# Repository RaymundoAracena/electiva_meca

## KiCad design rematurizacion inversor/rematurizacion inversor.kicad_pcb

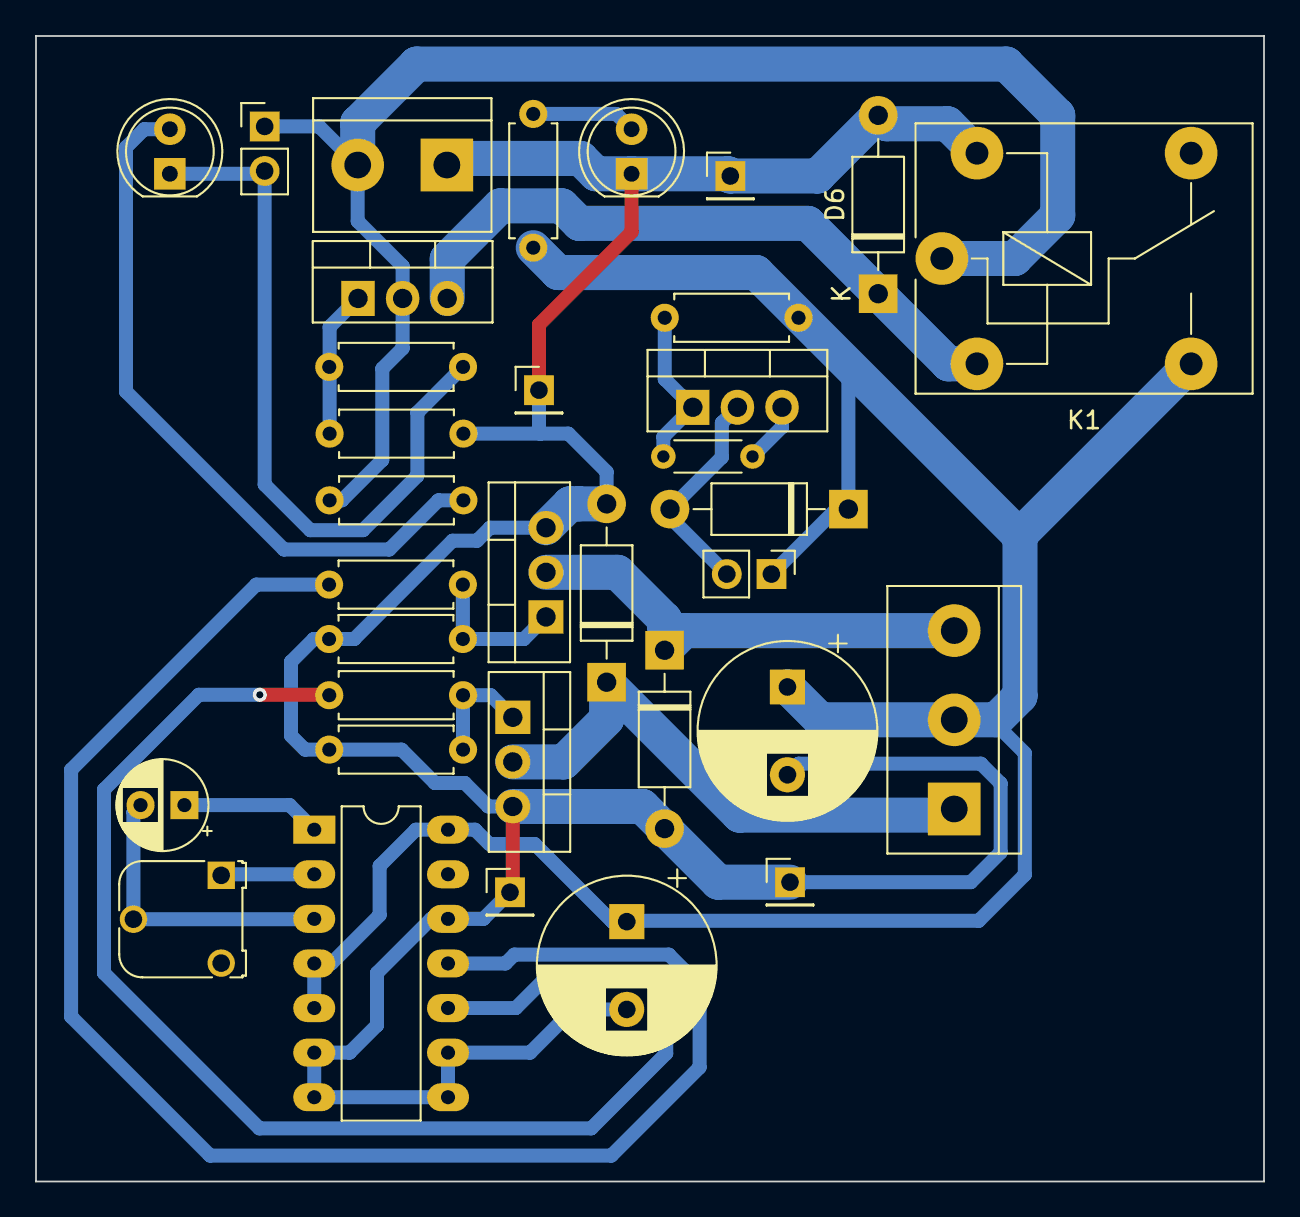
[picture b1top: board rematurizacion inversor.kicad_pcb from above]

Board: 2 copper layers, 69.9 x 65.2 mm, 34 parts (0 on the bottom side), 20 nets.

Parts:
C1, C2: 1000uF; CP_Radial_D10.0mm_P5.00mm
C3: 4.7uF; CP_Radial_D5.0mm_P2.50mm
D1, D2, D4, D6: 1N4007; D_DO-41_SOD81_P10.16mm_Horizontal
D3: on; LED_D5.0mm
D5: off; LED_D5.0mm
J1: DC; TerminalBlock_bornier-2_P5.08mm
J2: AC; TerminalBlock_bornier-3_P5.08mm
J3: sw; PinHeader_1x02_P2.54mm_Vertical
J4, J5, J6, J7: Screw_Terminal_01x01; PinHeader_1x01_P2.54mm_Vertical
K1: FINDER-36.11; Relay_SPDT_Finder_36.11
M1: Motor_DC; PinHeader_1x02_P2.54mm_Vertical
Q1, Q2, Q3, Q4: IRF3205; TO-220-3_Vertical
R1, R10: 330; R_Axial_DIN0207_L6.3mm_D2.5mm_P7.62mm_Horizontal
R2, R3, R4: 1k; R_Axial_DIN0207_L6.3mm_D2.5mm_P7.62mm_Horizontal
R5, R6, R9: 10k; R_Axial_DIN0207_L6.3mm_D2.5mm_P7.62mm_Horizontal
R7: PTC; R_Axial_DIN0204_L3.6mm_D1.6mm_P5.08mm_Horizontal
R8: 100; R_Axial_DIN0207_L6.3mm_D2.5mm_P7.62mm_Horizontal
RV1: 100k; Potentiometer_Runtron_RM-065_Vertical
U1: 4047; DIP-14_W7.62mm_LongPads

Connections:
+12P: C1.1, C2.1, D4.1 (K), J2.2, K1.14, M1.1 (+), R1.2, R2.1, U1.4 (~ASTABLE), U1.5 (ASTABLE), U1.14 (VDD)
+12V: J1.2, J3.1, K1.11, Q4.2 (D), R10.2
GND: Q3.3 (S), R7.2
GNDA: C1.2, C2.2, D1.2 (A), D2.2 (A), D3.1 (K), D6.2 (A), J1.1, J4.1, J5.1, J6.1, J7.1, K1.A2, Q1.3 (S), Q2.3 (S), R5.1, R6.1, R9.1, U1.6 (-TRIGGER), U1.7 (VSS), U1.8 (+TRIGGER), U1.9 (EXT_RESET), U1.12 (RETRIGGER)
unnamed: D1.1 (K), J2.3, Q2.2 (D)
unnamed: D2.1 (K), J2.1, Q1.2 (D)
unnamed: D3.2 (A), R1.1
unnamed: D4.2 (A), M1.2 (-), Q3.2 (D)
unnamed: D5.2 (A), R10.1
unnamed: D5.1 (K), J3.2, R8.2
unnamed: D6.1 (K), K1.A1, Q4.3 (S)
unnamed: Q1.1 (G), R3.2, R5.2
unnamed: Q2.1 (G), R4.2, R6.2
unnamed: Q3.1 (G), R2.2, R7.1
unnamed: Q4.1 (G), R8.1, R9.2
unnamed: C3.1, U1.1 (C)
unnamed: R3.1, U1.10 (Q)
unnamed: RV1.1, U1.2 (R)
unnamed: C3.2, RV1.2, U1.3 (RC_COMMON)
unnamed: R4.1, U1.11 (~Q)

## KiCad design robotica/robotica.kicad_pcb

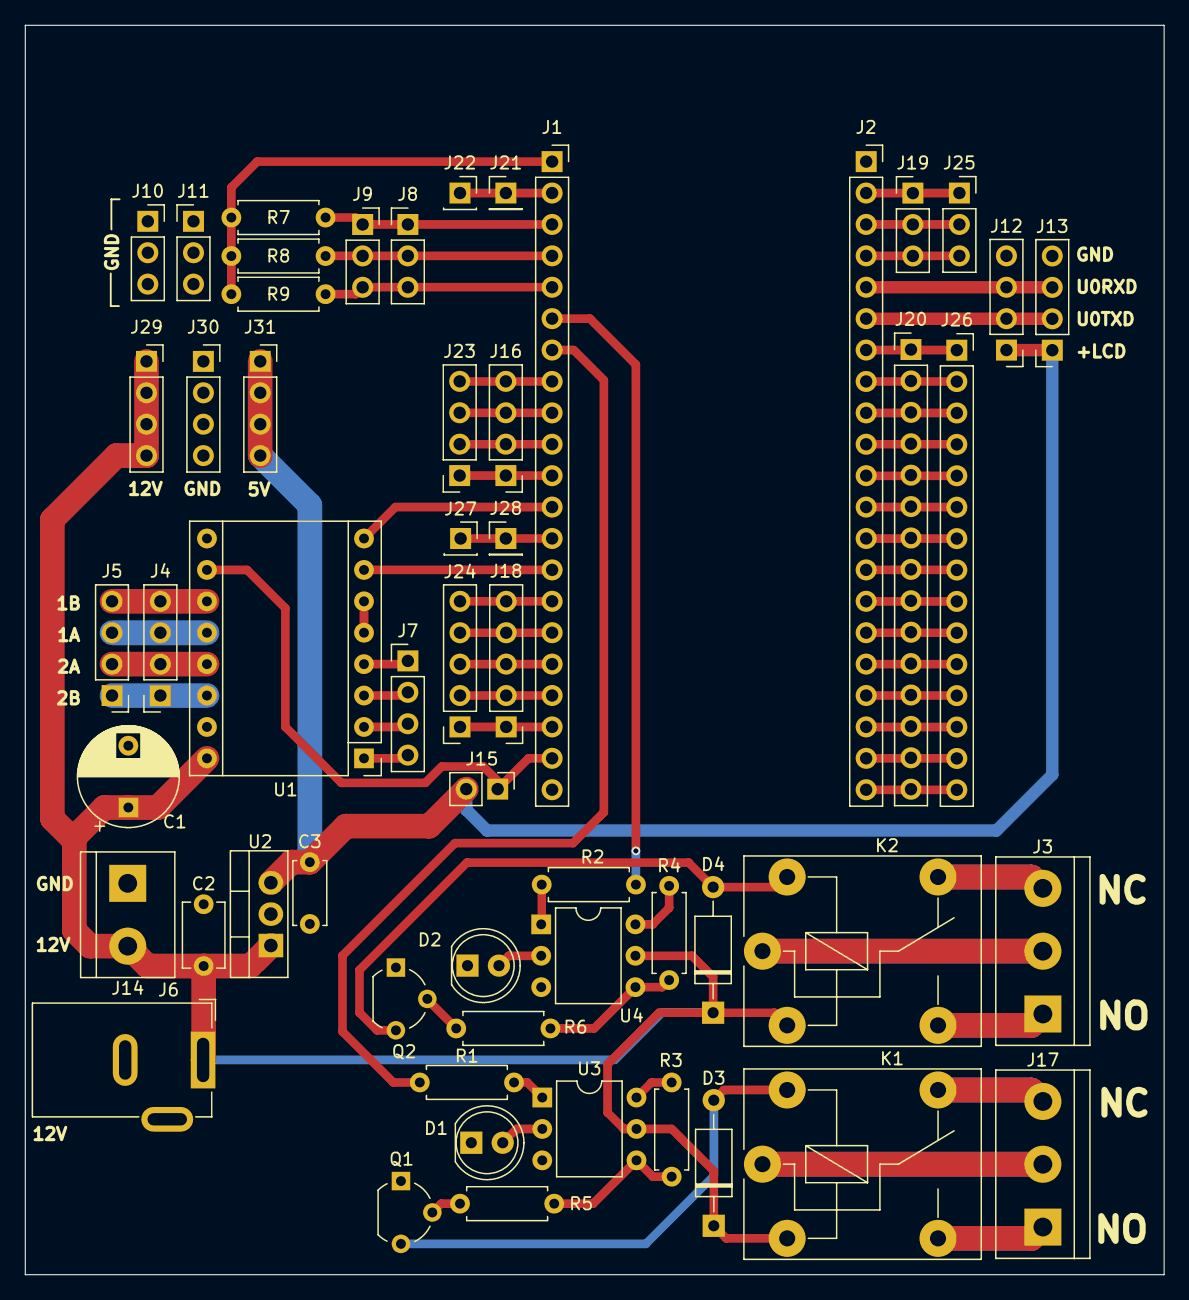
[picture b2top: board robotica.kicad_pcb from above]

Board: 2 copper layers, 92.1 x 101.0 mm, 55 parts (0 on the bottom side), 70 nets.

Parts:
C1: 47uF; CP_Radial_D8.0mm_P5.00mm
C2: 0.22uF; C_Disc_D5.1mm_W3.2mm_P5.00mm
C3: 0.1uF; C_Disc_D5.0mm_W2.5mm_P5.00mm
D1, D2: LED; LED_D5.0mm
D3, D4: >12v; D_A-405_P10.16mm_Horizontal
J1: IZQUIERDA; PinSocket_1x21_P2.54mm_Vertical
J2: DERECHA; PinSocket_1x21_P2.54mm_Vertical
J3, J17: salidas; TerminalBlock_bornier-3_P5.08mm
J4: MOTOR; PinSocket_1x04_P2.54mm_Vertical
J5: MOTOR; PinHeader_1x04_P2.54mm_Vertical
J6: 12V; BarrelJack_GCT_DCJ200-10-A_Horizontal
J7: driv; PinHeader_1x04_P2.54mm_Vertical
J8, J11, J19: Conn_01x03; PinHeader_1x03_P2.54mm_Vertical
J9, J10, J25: Conn_01x03; PinSocket_1x03_P2.54mm_Vertical
J12: LCD; PinHeader_1x04_P2.54mm_Vertical
J13: LCD; PinSocket_1x04_P2.54mm_Vertical
J14: 12V; TerminalBlock_bornier-2_P5.08mm
J15: POWER; PinHeader_1x02_P2.54mm_Vertical
J16: Conn_01x04; PinHeader_1x04_P2.54mm_Vertical
J18: Conn_01x05; PinHeader_1x05_P2.54mm_Vertical
J20: Conn_01x15; PinHeader_1x15_P2.54mm_Vertical
J21, J28: Conn_01x01; PinHeader_1x01_P2.54mm_Vertical
J22, J27: Conn_01x01; PinSocket_1x01_P2.54mm_Vertical
J23, J29, J30, J31: Conn_01x04; PinSocket_1x04_P2.54mm_Vertical
J24: Conn_01x05; PinSocket_1x05_P2.54mm_Vertical
J26: Conn_01x15; PinSocket_1x15_P2.54mm_Vertical
K1, K2: FINDER-36.11; Relay_SPDT_Finder_36.11
Q1, Q2: 2N3904; TO-92_Wide
R1, R2: 100; R_Axial_DIN0207_L6.3mm_D2.5mm_P7.62mm_Horizontal
R3, R4: 10k; R_Axial_DIN0207_L6.3mm_D2.5mm_P7.62mm_Horizontal
R5, R6: 1k; R_Axial_DIN0207_L6.3mm_D2.5mm_P7.62mm_Horizontal
R7, R8, R9: R; R_Axial_DIN0207_L6.3mm_D2.5mm_P7.62mm_Horizontal
U1: Pololu_Breakout-16_15.2x20.3mm
U2: LM7805_TO220; TO-220-3_Vertical
U3, U4: 4N35; DIP-6_W7.62mm

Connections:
+3V3: J1.1, R7.1, R8.1, R9.1
+5V: J1.20, J15.1, U1.10 (VDD)
+5VA: C3.1, J12.1, J13.1, J15.2, J31.1, J31.2, J31.3, J31.4, U2.3 (VO)
+12V: C1.1, C2.1, D3.1 (K), D4.1 (K), J6.1, J14.2, J29.1, J29.2, J29.3, J29.4, K1.A1, K2.A1, U1.16 (VMOT), U2.1 (VI), U3.5, U4.5
/DRIVER MOTOR/GPIO10: J1.12, U1.8 (DIR)
/DRIVER MOTOR/GPIO12: J1.14, U1.7 (STEP)
/FINAL RUN/GPIO1: J1.3, J8.1, J9.1, R7.2
/FINAL RUN/GPIO2: J1.4, J8.2, J9.2, R8.2
/FINAL RUN/GPIO3: J1.5, J8.3, J9.3, R9.2
/PANTALLA/GPIO43: J2.6, J12.2, J13.2
/PANTALLA/GPIO44: J2.5, J12.3, J13.3
/RELE/GPIO4: J1.6, R2.2
/RELE/GPIO5: J1.7, R1.2
/micro/GPIO0: J1.2, J21.1, J22.1
/micro/GPIO6: J1.8, J16.4, J23.4
/micro/GPIO7: J1.9, J16.3, J23.3
/micro/GPIO8: J1.10, J16.2, J23.2
/micro/GPIO9: J1.11, J16.1, J23.1
/micro/GPIO11: J1.13, J27.1, J28.1
/micro/GPIO13: J1.15, J18.5, J24.5
/micro/GPIO14: J1.16, J18.4, J24.4
/micro/GPIO15: J1.17, J18.3, J24.3
/micro/GPIO16: J1.18, J18.2, J24.2
/micro/GPIO17: J1.19, J18.1, J24.1
/micro/GPIO18: J2.21, J20.15, J26.15
/micro/GPIO19: J2.20, J20.14, J26.14
/micro/GPIO20: J2.19, J20.13, J26.13
/micro/GPIO21: J2.18, J20.12, J26.12
/micro/GPIO26: J2.17, J20.11, J26.11
/micro/GPIO33: J2.16, J20.10, J26.10
/micro/GPIO34: J2.15, J20.9, J26.9
/micro/GPIO35: J2.14, J20.8, J26.8
/micro/GPIO36: J2.13, J20.7, J26.7
/micro/GPIO37: J2.12, J20.6, J26.6
/micro/GPIO38: J2.11, J20.5, J26.5
/micro/GPIO39: J2.10, J20.4, J26.4
/micro/GPIO40: J2.9, J20.3, J26.3
/micro/GPIO41: J2.8, J20.2, J26.2
/micro/GPIO42: J2.7, J20.1, J26.1
/micro/GPIO45: J2.4, J19.3, J25.3
/micro/GPIO46: J2.3, J19.2, J25.2
/micro/RST: J2.2, J19.1, J25.1
GND: C1.2, C2.2, C3.2, D1.1 (K), D2.1 (K), J1.21, J2.1, J6.2, J10.1, J10.2, J10.3, J11.1, J11.2, J11.3, J12.4, J13.4, J14.1, J30.1, J30.2, J30.3, J30.4, Q1.1 (E), Q2.1 (E), U1.9 (GND), U1.15 (GND), U2.2 (GND)
unnamed: D1.2 (A), U3.2
unnamed: D2.2 (A), U4.2
unnamed: D3.2 (A), K1.A2, Q1.3 (C)
unnamed: D4.2 (A), K2.A2, Q2.3 (C)
unnamed: J3.1, K2.14
unnamed: J3.2, K2.11
unnamed: J3.3, K2.12
unnamed: J4.1, J5.1, U1.14 (2B)
unnamed: J4.2, J5.2, U1.13 (2A)
unnamed: J4.3, J5.3, U1.12 (1A)
unnamed: J4.4, J5.4, U1.11 (1B)
unnamed: J7.1, U1.4 (MS3)
unnamed: J7.2, U1.3 (MS2)
unnamed: J7.3, U1.2 (MS1)
unnamed: J7.4, U1.1 (ENA)
unnamed: J17.1, K1.14
unnamed: J17.2, K1.11
unnamed: J17.3, K1.12
unnamed: Q1.2 (B), R5.2
unnamed: Q2.2 (B), R6.2
unnamed: R1.1, U3.1
unnamed: R2.1, U4.1
unnamed: R3.1, U3.6
unnamed: R3.2, R5.1, U3.4
unnamed: R4.1, U4.6
unnamed: R4.2, R6.1, U4.4
unnamed: U1.5 (RESET), U1.6 (SLEEP)
